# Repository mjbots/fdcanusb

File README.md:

# mjcanfd-usb-1x / fdcanusb

The mjcanfd-usb-1x and fdcanusb provide access to a CAN-FD bus using a
USB 2.0 full speed connection.  They present two possible interfaces:

1. A `gs_usb` interface compatible with the Linux kernel `gs_usb` socketcan driver
2. serial-like interface over the USB port using the CDC ACM class, i.e. a virtual COM port.

The designs and firmware are licensed under the Apache 2.0 License.

 * 

Pre-assembled hardware can be purchased at https://mjbots.com/products/fdcanusb

## Usage with moteus tools and libraries

To use a device with moteus tools or libraries, first install the
relevant udev rule following the instructions in the top of the file:

* [70-fdcanusb.rules](70-fdcanusb.rules)

Second, just use the application.  moteus utilities like
`moteus_tool`, `tview`, and the python and C++ libraries will
automatically discover any connected devices and use the CDC protocol.

## USB CDC Protocol

Each command or response is a single newline terminated line, composed
of 7-bit ASCII encoded characters.  Every command sent from the client
to the device has a response which consists of an optional command
specific response followed by a final line consisting solely of `OK` or
`ERR <details>`.

### States

The device can be in one of two states.

1. *Bus Off*: This is the initial state of the device.  In this state,
no frames may be sent or received, but the device may be configured.

2. *Bus On*: In this state frames may be sent and received, but
configuration is locked out.

## Commands

Sample commands are prefixed with `>` to show the data sent from the
client to the device and `<` to show the values sent from the device
to the client.  Those characters are for illustrative purposes only,
and are not present in actual communications.

### *conf*

The "conf" command is used to read and set configuration values.  It
has several subcommands.

#### *conf enumerate*

This emits all current configuration values one after another.

#### *conf get*

This queries the value of one specific configuration item.

```
>conf get sample.value
<31235
<OK
```

#### *conf set*

This sets the value of one specific configuration itme.

```
>conf set sample.value 1234
<OK
```

#### *conf load*

This loads all persistent configuration from the persistent storage.

```
>conf load
<OK
```

#### *conf write*

This stores all configuration values to persistent storage.  They will
then be the default when the device is powered on the in the future.

```
>conf write
<OK
```

#### *conf default*

Reset all configuration values to their "default" state.

```
>conf default
<OK
```

### can

#### *can on*

Enter the "Bus On" state.  All configurable values are validated and
put into place.  This results in an error if the device is already in
the "Bus On" state.

#### *can off*

Enter the "Bus Off" state.  Transmission and reception of CAN messages
is halted, and configurable values may be changed.

#### *can std*

Send a standard CAN frame.  The following format is used.

`can std <HEXID> <HEXDATA> <options>`

`options` may be zero or more of the following optionally separated by
spaces.

1. *B/b* require/disable bitrate switching
2. *F/f* require/disable FDCAN format
3. *R/r* require/disable remote frame

#### *can ext*

Send an extended CAN frame.  The following format is used.

`can ext <HEXID> <HEXDATA> <options>`

The allowable options are the same as for `can std`.

#### *can send*

Just like `std` or `ext`, but auto-detect the ID type.

#### *can status*

Report the current mode and status of various flags.

```
>can status
<mode:BUSON
<OK
```

### Receiving CAN Frames

When in the "Bus On" state, the device may spontaneously emit the
following lines upon receipt of valid CAN frames or other errors.

#### *rcv*

A CAN frame has been received.

```
<rcv <HEXID> <HEXDATA> <flags>
```

`flags` may be zero of more of the following separated by spaces:

1. *E/e* frame was received with extended/classic ID
1. *B/b* frame was received with/without bitrate switching
2. *F/f* frame was received in fdcan/classic mode
3. *R/r* frame was remote/data frame
4. tNNNNN timestamp of receipt measured in microseconds
5. fNN integer ID of which filter matched this frame

### Configurable Values

The following items may be configured.

* *can.bitrate* - The bitrate used for the CAN frame (or header only
  if bitrate switching is used.
* *can.fd_bitrate* - The bitrate used for the data and CRC field when
  bitrate switching is used.
* *can.sample_point* - The sample point for the nominal part of the
  CAN frame.  moteus requires 0.666, some other systems default to
  0.75, 0.8, or 0.87.
* *can.fd_sample_sample* - The sample point for the data (BRS) part of
  the CAN frame.  moteus requires 0.666, other systems may require
  alternate settings.
* *can.automatic_retransmission* - When true/non-zero, frames will be
  retried until acknowledged.
* *can.fdcan_frame* - By default, send frames in FDCAN mode
* *can.bitrate_switch* - By default, switch to the `can.fd_bitrate`
  for the data and CRC fields.
* *can.restricted_mode* - Only transmit acknowledgements.
* *can.bus_monitor* - Transmit nothing.
* *can.termination* - Enable the onboard terminator
* *can.autostart* - Enter BusOn immediately at power-on
* *can.autorecover* - Automatically recover from bus off events

* *can.global.std_action*
* *can.global.ext_action*
* *can.global.remote_std_action*
* *can.global.remote_ext_action*
  * 0/1 - accept
  * 2 - reject

* *can.filter.N.id1* - first ID
* *can.filter.N.id2* - second ID or bitmask
* *can.filter.N.mode*
  * 0 - range
  * 1 - exact match
  * 2 - bitmask
* *can.filter.N.type*
  * 0 - standard
  * 1 - extended
* *can.filter.N.action*
  * 0 - disable
  * 1 - accept
  * 2 - reject

## gs_usb interface

To use the device with a socketcan driver on Linux, the normal socketcan utilities can be used.  For instance, to bring up an interface compatible with moteus (not usually required because moteus tools and libraries will by default use the CDC interface), you would do:

```bash
ip link set can0 up type can \
  bitrate 1000000 dbitrate 5000000 \
  sjw 10 dsjw 5 \
  sample-point 0.666 dsample-point 0.666 \
  fd on
```

Then, all messages received can be displayed with:

```bash
candump can0
```

## Building firmware

To build the firmware on an Ubuntu 22.04 or newer system.

```
sudo apt install curl openocd
./tools/bazel build //...
```

To flash:

```
./flash.py
```

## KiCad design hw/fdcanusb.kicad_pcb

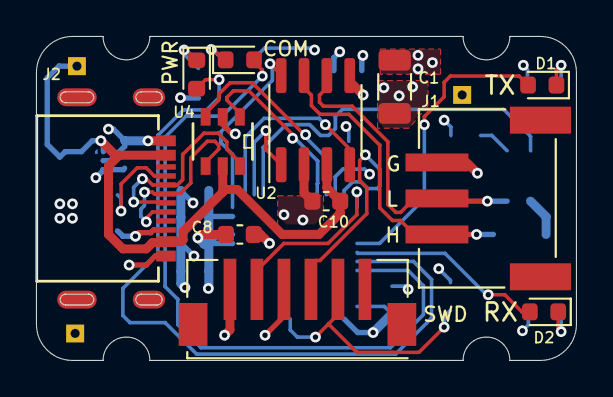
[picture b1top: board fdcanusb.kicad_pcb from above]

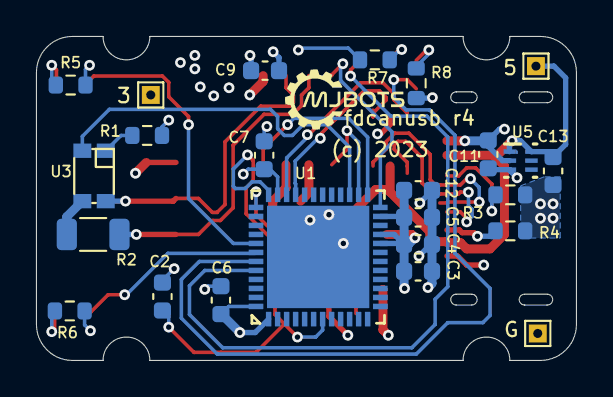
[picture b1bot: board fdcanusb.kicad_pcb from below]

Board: 4 copper layers, 30.0 x 18.0 mm, 36 parts (24 on the bottom side), 28 nets.

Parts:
C1: 10uF; C_1206_3216Metric
C2, C4, C6, C7, C8, C9, C10, C12: 0.1uF; C_0603_1608Metric
C3: 4.7uF; C_0603_1608Metric
C5, C11, C13: 1uF; C_0603_1608Metric
D1, D3: GREEN; LED_0603_1608Metric
D2, D4: RED; LED_0603_1608Metric
J1: Conn_01x03; JST_S3B-PH-SM4-TB(LF)(SN)
J2: 216990-0002; 216990-0002_MOL
J3, J4, J5: Conn_01x01; TestPoint_THTPad_1.0x1.0mm_Drill0.5mm
R1: 330; R_0603_1608Metric
R2: 110; R_1206_3216Metric
R3, R4: 5.1k; R_0603_1608Metric
R5, R6, R7, R8: 220; R_0603_1608Metric
SWD1: B6B-ZR-SM4-TF(LF)(SN); B6B-ZR-SM4-TFLFSN
U1: STM32G474CEU6; UFQFPN-48_7X7X0P55MM
U2: TCAN1057AEVDRQ1; SOIC-8_3.9x4.9mm_P1.27mm
U3: TLP3317
U4: USBLC6-2SC6; SOT23-6L_STM
U5: TLV70233DSER; DSE0006A

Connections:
+3V: C1.1, C3.1, C4.1, C5.1, C6.1, C7.1, C8.1, C9.1, C11.1, C12.1, J4.1, R1.1, SWD1.6, U1.1 (VBAT), U1.20 (VREF+), U1.21 (VDDA), U1.23 (VDD), U1.35 (VDD), U1.48 (VDD), U2.5 (VIO), U5.3 (OUT)
+5V: C10.1, C13.1, J2.A4/B9 (VBUS), J2.B4/A9 (VBUS), J5.1, U2.3 (VCC), U4.5, U5.1 (IN), U5.6 (EN)
/CAN/CAN_N: J1.2, U2.6 (CANL), U3.4
/CAN/CAN_P: J1.1, R2.2, U2.7 (CANH)
/CAN/CAN_RX: U1.25 (PB12), U2.4 (RXD)
/CAN/CAN_STB: U1.24 (PB11), U2.8 (STB)
/CAN/CAN_TERM: U1.27 (PB14), U3.2
/CAN/CAN_TX: U1.26 (PB13), U2.1 (TXD)
/LED Debug/LED_CAN_RX: D2.2 (A), U1.42 (PB4)
/LED Debug/LED_CAN_TX: D1.2 (A), U1.41 (PB3)
/LED Debug/LED_COM: D3.2 (A), U1.44 (PB6)
/LED Debug/LED_PWR: D4.2 (A), U1.43 (PB5)
/Power Input/USB_F_N: U1.33 (PA11), U4.1
/Power Input/USB_F_P: U1.34 (PA12), U4.3
/Power Input/USB_N: J2.A7 (DN1), J2.B7 (DN2), U4.6
/Power Input/USB_P: J2.A6 (DP1), J2.B6 (DP2), U4.4
/stm32g4/NRST: C2.1, SWD1.2, U1.7 (PG10-NRST)
/stm32g4/SWCLK: SWD1.5, U1.37 (PA14)
/stm32g4/SWDIO: SWD1.3, U1.36 (PA13)
GND: C1.2, C2.2, C3.2, C4.2, C5.2, C6.2, C7.2, C8.2, C9.2, C10.2, C11.2, C12.2, C13.2, J1.3, J2.A1/B12 (GND), J2.B1/A12 (GND), J3.1, R3.2, R4.2, R5.2, R6.2, R7.2, R8.2, SWD1.4, U1.49 (EPAD), U2.2 (GND), U4.2, U5.2 (GND)
unnamed: D1.1 (K), R5.1
unnamed: D2.1 (K), R6.1
unnamed: D3.1 (K), R7.1
unnamed: D4.1 (K), R8.1
unnamed: J2.A5 (CC1), R3.1
unnamed: J2.B5 (CC2), R4.1
unnamed: R1.2, U3.1
unnamed: R2.1, U3.3

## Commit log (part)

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2019-10-07 Initial version of fdcanusb
2019-10-07 Finish BOM and fine silk placement
2019-10-07 More BOM tweaks
2019-10-07 Mark pin 1 on optocoupler
2019-10-07 Switch to actually using a micro USB connector
2019-11-18 Update to use correct STM32 pinout
2019-11-18 Record the r1 version
2019-11-18 Use the digikey number for DB9, since MF can find it
2019-11-27 Initial firmware stub
2019-11-30 Slight refactoring towards something more usable
2019-11-30 Add some auxiliary helper scripts
2019-11-30 First draft of protocol
2019-11-30 Import and stub out the persistent configuration library
2019-12-01 Don't rely on an uninitialized timer init structure
2019-12-02 Use the correct directory in debug.gdb
2019-12-03 Non-working checkpoint
2019-12-03 This at least can send
2019-12-03 Nominally support any pin or DMA channel
2019-12-03 Actually likely work with any uart
2019-12-03 Hook up receiving, and enable the channel for real
2019-12-03 Idle detection
2019-12-03 Make stm32_serial look more like the thing that works
2019-12-03 Switch to a temporary debugging version to exercise reads and writes
2019-12-03 Slight reformatting and prep for switching to Stm32Serial
2019-12-03 Switch to using Stm32Serial after fixing it to use proper #defines
2019-12-04 Stop using the HAL for reads and instead use a circular buffer
2019-12-04 Update to an mjlib which reports more consistent error messages
2019-12-04 Stub out CanManager
2019-12-04 Print out received CAN frames
2019-12-04 Implement some of the options
2019-12-04 Update to an mjlib that has working array-of-structure support
2019-12-04 Pass through filter values
2019-12-04 First pass at being able to send frames
2019-12-04 Grab a bugfix in mjlib
2019-12-04 acknowledge CAN sends with an OK
2019-12-04 IDs are supposed to always be hex
2019-12-04 Implement status and bitrate setting
2019-12-04 Implement flash storage for persistent settings
2019-12-07 Update mjlib and add autostart
2019-12-08 Update the maximum line length to 300
    This is useful, since sending a 64 byte can frame takes at least 128
    bytes plus the start and end of the command and optional flags.
2019-12-09 Stub of USB CDC driver
2019-12-10 Oops, this was meant to fall through
2019-12-10 Basic USB CDC communication seems to work
2019-12-11 Use the correct CAN peripheral for the pins selected
2019-12-11 Use the CAN pins on the actual device
2019-12-11 Implement soft termination and ensure other pins are at known values
2019-12-11 Implement RX and TX light
2019-12-11 Implement power and com LEDs
2019-12-11 r2 of fdcanusb board
2019-12-11 Fix DB9 pinout
2019-12-12 Add a global license file
2019-12-12 Properly read data when a single CDC frame gives us more than 1 byte
2019-12-12 Add TODO
2019-12-12 Add travis integration
2019-12-12 I have no unit tests currently, so just build
2019-12-12 Add a travis badge
2020-01-13 Don't try to read if no one is ready for it
2020-01-14 Add a sample udev rule
2020-01-14 Make the bazel flash target actually work
2020-01-14 Update TODO
2020-01-15 Report the git version as well as the device serial number
2020-01-17 Fix the git dirty indication
2020-01-17 gitinfo should work without stamping too
2020-01-23 Capture r2.1
2020-01-24 Update to r2.2
    This just reduces the size of the PCB so it doesn't hang out so far
    under the DB-9 connector.
2020-01-24 Draft enclosure
2020-01-27 Switch LED resistors back to 220s
2020-02-13 Add build and flash instructions
2020-02-28 Properly parse the DLC of non-FD frames
2020-02-28 Provide more bitrate options
    This provides knobs to make the device more interoperable with other
    CAN devices.
2020-02-29 Slightly refactor to make this more similar to other projects
2020-02-29 Update copyright years
2020-02-29 Incorporate yet more things from other projects
2020-03-07 Update udev rule to be more specific
2020-10-04 Improve the instructions for reloading the udev rule
    On 20.04, just --reload-rules by itself isn't enough
2020-10-22 A minimal tool to bridge fdcanusb and socketcan
    This has worked in one basic test, but hasn't received much testing
    otherwise. It bridges a virtual CAN interface and the fdcanusb.
2020-10-22 Add instructions for how to create a vcan interface
2020-11-29 Implement hsi clock trimming
2020-12-10 If we can't write yet, don't bother pulling off a packet
    This logic previously could cause the fdcanusb to "drop" packets, if
    one came in while it was in the middle of sending something to the USB
    bus. Now it will at least use the FDCAN peripheral's buffers to hold
    the frames until the USB write is complete. Overruns are still
    possible, but at least our buffer size is non-zero.
2020-12-26 Record the build timestamp in the firmware
2021-01-17 Make DB9 have plated holes for retaining clips
    This should improve the mechanical strength of the DB9 connector when
    installed
2021-01-18 Tweak silk position
2021-01-18 r2.3 as sent for mf
2021-02-15 Note where hardware can be purchased
2021-05-27 Support recording a uuid in persistent storage
2021-06-03 Update to use a newer bazel_deps with a valid boost URL
2022-01-15 Fix off by one error
2022-01-15 fdcanusb_daemon: Work with serial port in raw mode
    If the daemon was the only thing that opened the serial port, it would
    not be in raw mode. The kernel would echo some of the characters the
    device sent back to it, which confused things greatly.
2022-11-02 r3.0 as sent to oshpark
2022-11-02 Update PCB to fdcanusb r2.4 * All components are increased to minimum 0603 * Switch to the SOIC package for the CAN transceiver, which is easier to get * Switch to 6mil min space/trace
2022-11-02 More fine silk and slight routing
2022-11-02 Fix resistor footprint
2022-11-02 Fine silk placement
2022-11-02 SCHEMATIC ONLY work on more CAN transceiver variants
    Update schematic, but not PCB, to accept the TCAN1057AEV in addition
    to the 3.3V native variants.
2022-11-02 Nominally complete fdcanusb w/ support for all known SOIC8/SOT8 CAN
    * This will work with all the 3.3V and 5V 8 pin parts I know of with
    no more than different resistor populations.
2022-11-02 More silk tweaks
2022-11-03 Add a decoupling cap on VIO
2022-11-03 r2.5 as sent to oshpark
2022-11-21 Add support for delay compensation and enable it by default
    This is required to operate on boards with the TCAN1057, but still
    works on older fdcanusbs as well.
2023-05-18 Be more specific in how the udev rule should be installed
2023-08-28 Update bazel, rules_mbed, and mjlib
2023-09-19 Remove the never-produced r3
2024-02-02 Update required OS and list `apt` instruction
    22.04 isn't strictly required, but it is the first LTS with a suitable
    openocd built in.
2024-02-02 Really, some dependencies are required, so remove that clause
2024-03-06 WIP of a KiCad fdcanusb r4
2024-03-06 Maybe complete routing and passes all DRC
2024-03-06 r4: Add board label and fine silk tune
2024-03-06 Re-run DRC and zone fill, set layers
2024-03-06 Rename board to mjcanfd-usb-1x
2024-03-06 Add debug pads for power rails
2024-03-06 Make BOM match MF headings
2024-03-06 Remove fp-info-cache from git
2024-03-06 r4.1 as mfg
2024-03-06 Update DRC exclusions
2024-03-06 r4 exclusions
2024-03-06 r4.1: Swith to an actual SMT USB-C connector
2024-03-06 Add title block and update rev to r4.2
2024-03-06 Set up kicadbom and make a pass at filling in all bom entries
2024-03-06 r4: More work to get silk off vias
2024-03-06 DRC exclusions
2025-01-05 fdcanusb_daemon: Switch to using blocking I/O
    Previously, the program would error if the fdcanusb adapter was busy, due to EAGAIN return value from the write call.
    This would occationally happen during periods with messages in rapid succession.
    By switching to blocking IO, the program will instead wait for the device to become ready.
2025-01-14 Implement `can.autorecover`
    This can be used to make communication more reliable if your CAN-FD
    bus has electrical problems.
2025-04-24 Update bazel_deps to get new boost URL
2025-05-02 include cstdint
2025-07-21 Allow configuration of the sample point
2025-09-12 Add buffers and optimize performance
    When receiving frames, we now have at a minimum a 2k buffer of
    formatted ASCII output, which will in practice provide for at least 8
    frames and possibly many more.
    We were spending *a lot* of time formatting the string responses. Fix
    that by stopping usage of sprintf.
2025-09-13 Switch to a more useful flashing script that can take an arbitrary .elf
2025-09-13 Update mjlib
    This gets a more efficient micro::AsyncReadUntil which drastically
    improves the runtime performance of the fdcanusb when processing many
    outgoing messages.
2025-09-15 Implement a 32 position outgoing CAN queue
    It is pretty easy to fill up the 3 position onboard one when querying
    many devices at a slow bitrate.
2025-09-19 Switch the fdcanusb to use auto-retransmit by default
    This will make it able to reliably address more than 2 or 3 devices.
    To get around the problems caused by sending never-acknowledged
    frames, we cancel all frames in the hw queue after by default 50ms
    after the last frame was entered into the hw queue.
2025-09-19 Update the FIFO so that it can be used in its entirety.
2025-09-19 Add a tool to make release images
2025-09-24 The release tool should copy the .bin file too
2025-11-30 Add CI
2026-01-08 Add some HIL tests for basic fdcanusb and gs_usb functionality
2026-01-08 Add an integration test covering buffer backups
    Ensure that if either of the two interfaces is never opened, it
    doesn't interfere with receiving large number of frames on the other
    interface.
2026-01-08 gs_usb: Implement one-shot mode
    This was tested manually on the fixture with the legacy device in bus monitor mode and using:
    `ip link set can0 up type can one-shot on`
2026-01-08 Basic support for also enumerating as a gs_usb device
    This means that the fdcanusb/mjcanfd-usb-1x will present as a
    "composite USB" device with two distinct IADs. One emulates the
    gs_usb protocol used by the Linux gs_usb driver, the other is a CDC
    interface as before.
    The two interfaces are designed to be usable in parallel or
    separately, although if used in parallel, some things like bus/timing
2026-01-08 Provide a compile-time disabled debug print UART
    This re-purposes the LED TX line, so it can't be enabled all the time,
    but on blue-wired boards gets you access to a relatively high speed
    debug console.
2026-01-08 gs_usb: Implement listen-only mode
    This was tested using `ip link set can0 up type can listen-only on`.
2026-01-08 Remove the fdcanusb_daemon driver
    Now that we have a native socketcan interface, there is no need for
    this translation layer in order to get socketcan support.
2026-01-08 gs_usb: Implement loopback and error count reporting
    Loopback was tested by using `loopback on` or `loopback off` on the
    test fixture.
    Error reporting was tested by using `ip -details link show can0`. For
    tx errors, the other device was set in bus monitor mode, which maxed
    out errors, then when disabled, errors decrease by one per frame sent.
    For rx errors, the other device was set with a CAN 2.0 sample point of
2026-01-08 gs_usb: Implement software controlled termination support
    This was tested manually with a multimeter and:
    * ip link set can0 type can termination 120
    and
    * ip link set can0 type can termination 0
2026-01-08 Report filter matches with 'x' to distinguish it from 'f'
2026-02-16 Only report data back to the host when we actually have it
    Since the very first fdcanusb release, this has resulted in an
    infinite loop causing the host controller to request packets as fast
    as possible. It probably explains why there have been sporadic
    compatibility issues, as some hardware is busted and doesn't like
    operating at maximum request rate indefinitely.

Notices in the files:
hw/fdcanusb.kicad_pcb:
(c) 2023
parts and their libraries:
Copyright 2021 Accelerated Designs. All rights reserved.
